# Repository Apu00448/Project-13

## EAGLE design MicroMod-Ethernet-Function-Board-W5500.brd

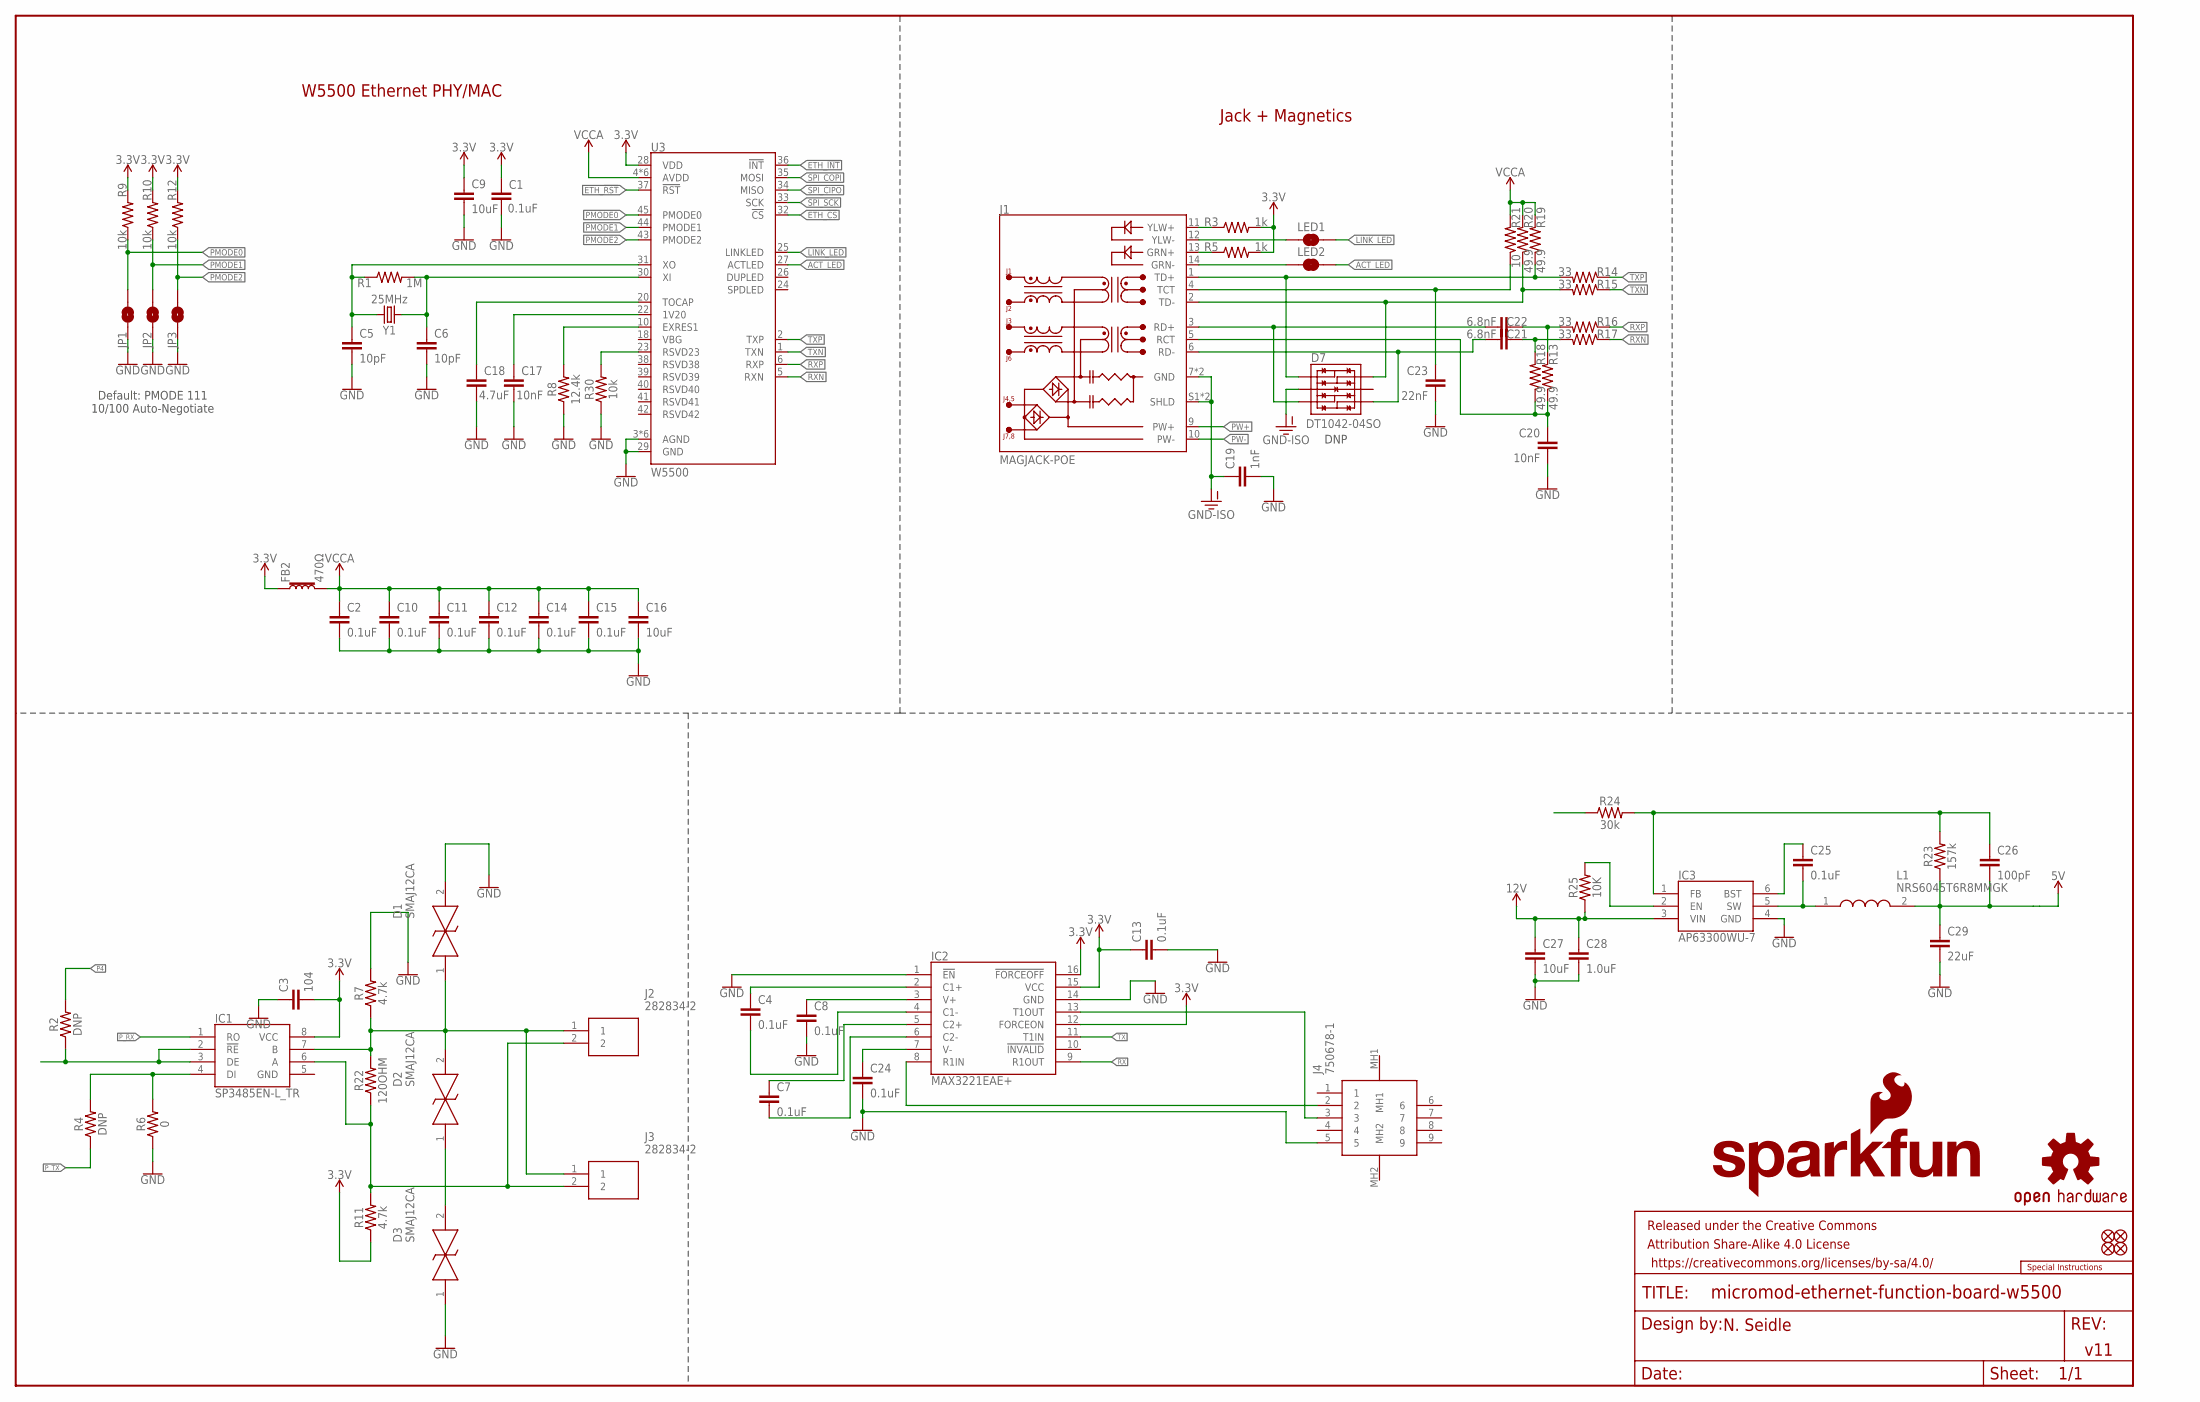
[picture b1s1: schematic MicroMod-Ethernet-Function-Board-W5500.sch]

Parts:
C1, C2, C10, C11, C12, C14, C15: 0.1uF; 0603
C3: 104; 0402-TIGHT_NO_CREAM
C4, C7, C8, C13, C24, C25: 0.1uF; 0402-TIGHT
C5, C6: 10pF; 0603
C9, C16: 10uF; 0603
C17, C20: 10nF; 0603
C18: 4.7uF; 0603
C19: 1nF; 1206
C21, C22: 6.8nF; 0603
C23: 22nF; 0603
C26: 100pF; 0402-TIGHT
C27: 10uF; 0402-TIGHT
C28: 1.0uF; 0402-TIGHT
C29: 22uF; 0603
D1, D2, D3: SMAJ12CA; DIONM5026X229N
D7: DT1042-04SO; SOT-23-6
FB2: 470Ω; 0603
FD1, FD2, FD3, FD4: FIDUCIALUFIDUCIAL; FIDUCIAL-MICRO
FRAME1: FRAME-LEDGER; CREATIVE_COMMONS
IC1: SP3485EN-L_TR; SOIC127P600X175-8N
IC2: MAX3221EAE+; SOP65P778X199-16N
IC3: AP63300WU-7; SOT95P280X90-6N
J1: MAGJACK-POE; MAGJACK-SYM_LED
J2, J3: 282834-2; 282834-2_1
J4: 750678-1; 7506781
JP1, JP2, JP3: JUMPER-SMT_2_NO_SILK; SMT-JUMPER_2_NO_SILK
L1: NRS6045T6R8MMGK
LED1, LED2: JUMPER-SMT_2_NC_TRACE_SILK; SMT-JUMPER_2_NC_TRACE_SILK
LOGO1: SFE_LOGO_NAME_FLAME.1_INCH; SFE_LOGO_NAME_FLAME_.1
LOGO2: SPECIAL_INSTRUCTIONS-ORDERING; ORDERING_INSTRUCTIONS
LOGO3: OSHW-LOGOMINI; OSHW-LOGO-MINI
R1: 1M; 0603
R2, R4: DNP; 0402-TIGHT
R3, R5: 1k; 0603
R6: 0; 0402-TIGHT
R7, R11: 4.7k; 0402-TIGHT
R8: 12.4k; 0603
R9, R10, R12, R30: 10k; 0603
R13, R18, R19, R20: 49.9; 0603
R14, R15, R16, R17: 33; 0603
R21: 10; 0603
R22: 120OHM; 0603
R23: 157k; 0402-TIGHT
R24: 30k; 0402-TIGHT
R25: 10K; 0402-TIGHT
U3: W5500; LQFP-48
Y1: 25MHz; CRYSTAL-SMD-2.0X1.6MM

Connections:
3.3V: C1.1, C3.2, C9.1, C13.1, FB2.1, IC1.8 (VCC), IC2.12 (FORCEON), IC2.15 (VCC), IC2.16 (!FORCEOFF), R3.2, R5.2, R9.2, R10.2, R11.1, R12.2, U3.28 (VDD)
5V: C26.2, C29.1, L1.2, R23.1
12V: C27.1, C28.1, IC3.3 (VIN), R25.1
ACT_LED: LED2.2, U3.27 (ACTLED)
ETH_!CS!: U3.32 (!CS!)
ETH_!INT!: U3.36 (!INT!)
ETH_!RST!: U3.37 (!RST!)
GND: C1.2, C2.2, C3.1, C5.2, C6.2, C8.2, C9.2, C10.2, C11.2, C12.2, C13.2, C14.2, C15.2, C16.2, C17.2, C18.2, C19.2, C20.2, C23.2, C24.2, C27.2, C28.2, C29.2, D1.2, D3.1, IC2.1 (!EN), IC2.14 (GND), IC3.4 (GND), J4.5, JP1.1, JP2.1, JP3.1, R6.1, R7.2, R8.1, R30.1, U3.3 (AGND), U3.9 (AGND), U3.14 (AGND), U3.16 (AGND), U3.19 (AGND), U3.29 (GND), U3.48 (AGND)
GND-ISO: C19.1, D7.2 (VSS), J1.7 (GND), J1.8 (GND), J1.S1 (SHLD), J1.S2 (SHLD)
LINK_LED: LED1.2, U3.25 (LINKLED)
unnamed: C5.1, R1.1, U3.31 (XO), Y1.1
unnamed: C6.1, R1.2, U3.30 (XI), Y1.3 (2)
unnamed: J1.14 (GRN-), LED2.1
unnamed: J1.12 (YLW-), LED1.1
unnamed: C7.1, IC2.5 (C2+)
unnamed: IC1.2 (!RE), IC1.3 (DE), R2.1
unnamed: IC1.4 (DI), R4.2, R6.2
unnamed: J1.13 (GRN+), R5.1
unnamed: C7.2, IC2.6 (C2-)
unnamed: J1.11 (YLW+), R3.1
unnamed: IC1.6 (A), J2.2, J3.2, R11.2, R22.1
unnamed: C4.2, IC2.4 (C1-)
unnamed: R8.2, U3.10 (EXRES1)
unnamed: C4.1, IC2.2 (C1+)
unnamed: C17.1, U3.22 (1V20)
unnamed: C18.1, U3.20 (TOCAP)
unnamed: R30.2, U3.23 (RSVD23)
unnamed: C8.1, IC2.3 (V+)
unnamed: D1.1, D2.2, IC1.7 (B), J2.1, J3.1, R7.1, R22.2
unnamed: D2.1, D3.2
unnamed: C24.1, IC2.7 (V-)
unnamed: C25.2, IC3.5 (SW), L1.1
unnamed: IC2.8 (R1IN), J4.2
unnamed: IC2.13 (T1OUT), J4.3
unnamed: C25.1, IC3.6 (BST)
unnamed: C26.1, IC3.1 (FB), R23.2, R24.2
unnamed: IC3.2 (EN), R25.2
P4: R2.2
PMODE0: JP1.2, R9.1, U3.45 (PMODE0)
PMODE1: JP2.2, R10.1, U3.44 (PMODE1)
PMODE2: JP3.2, R12.1, U3.43 (PMODE2)
PW+: J1.9 (PW+)
PW-: J1.10 (PW-)
P_RX: IC1.1 (RO)
P_TX: R4.1
RCT: C20.1, J1.5 (RCT), R13.1, R18.1
RD+: C22.2, D7.3 (IO2), J1.3 (RD+)
RD-: C21.2, D7.4 (IO3), J1.6 (RD-)
RX: IC2.9 (R1OUT)
RXN: R17.1, U3.5 (RXN)
RXN1: C21.1, R17.2, R18.2
RXP: R16.1, U3.6 (RXP)
RXP1: C22.1, R13.2, R16.2
SPI_CIPO: U3.34 (MISO)
SPI_COPI: U3.35 (MOSI)
SPI_SCK: U3.33 (SCK)
TCT: C23.1, J1.4 (TCT), R21.1
TD+: D7.1 (IO1), J1.1 (TD+), R14.2, R19.1
TD-: D7.6 (IO4), J1.2 (TD-), R15.2, R20.1
TX: IC2.11 (T1IN)
TXN: R15.1, U3.1 (TXN)
TXP: R14.1, U3.2 (TXP)
VCCA: C2.1, C10.1, C11.1, C12.1, C14.1, C15.1, C16.1, FB2.2, R19.2, R20.2, R21.2, U3.4 (AVDD), U3.8 (AVDD), U3.11 (AVDD), U3.15 (AVDD), U3.17 (AVDD), U3.21 (AVDD)

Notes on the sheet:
N. Seidle
v11
W5500 Ethernet PHY/MAC
Default: PMODE 111 10/100 Auto-Negotiate
Jack + Magnetics
DNP

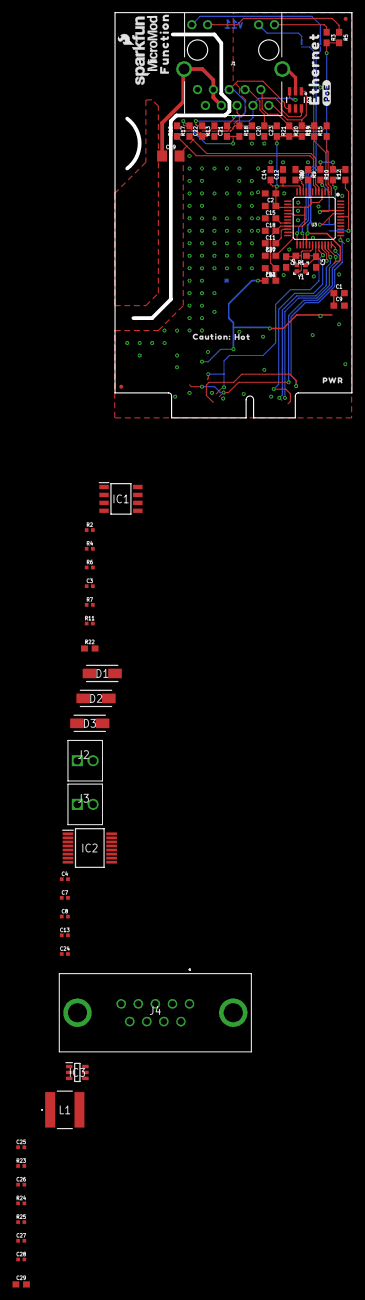
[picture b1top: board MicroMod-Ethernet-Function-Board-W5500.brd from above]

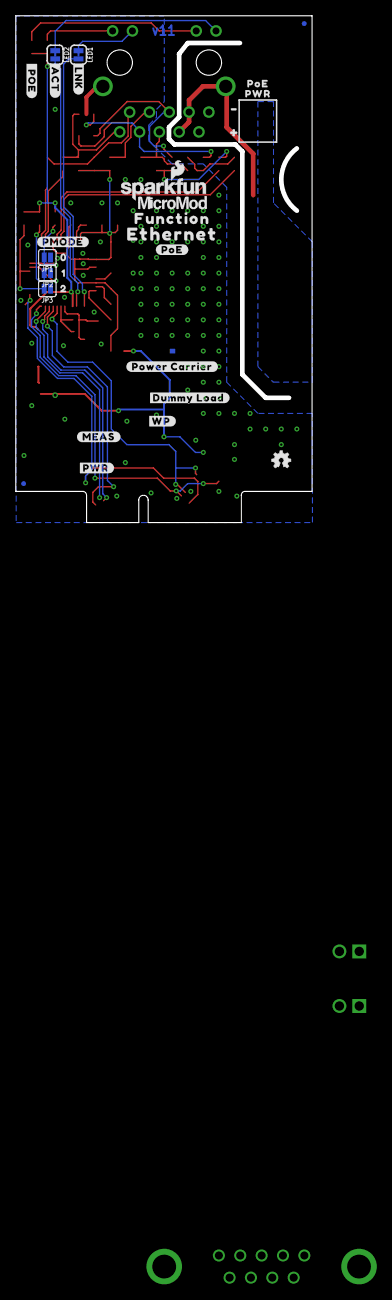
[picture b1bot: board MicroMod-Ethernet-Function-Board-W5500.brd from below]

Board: 2 copper layers, 38.0 x 65.0 mm, 111 parts (29 on the bottom side), 50 nets.

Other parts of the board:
LOGO4: SFE_LOGO_NAME_FLAME.1_INCH; SFE_LOGO_NAME_FLAME_.1
U$1, U$17: ETHERNET0
U$2, U$18: #POE#0
U$3: #POWER_CARRIER#0
U$5: #DUMMY_LOAD#0
U$6: #WP#0
U$7: PWR0
U$8: #ACT#0
U$9: POE0
U$12: #LNK#1
U$13: #PMODE#0
U$14: 01
U$15: 12
U$16: 23
U$19: #0
U$20: CAUTION#0
U$21: HOT#1
U$22: #PWR#0
U$23: #_POE#0
U$24: PWR1
U$25: #1
U$26, U$27: FUNCTION0
U$28: #MEAS#3
U$37, U$63: MICROMOD_LOGO_.35

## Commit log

2024-01-03 MicroMod-Ethernet-Board_ Eagle

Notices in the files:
parts and their libraries:
SparkFun-Aesthetics: Licensing: Creative Commons ShareAlike 4.0 International - https://creativecommons.org/licenses/by-sa/4.0
SparkFun-Aesthetics: Released under the Creative Commons Attribution Share-Alike 4.0 License
SparkFun-Aesthetics: https://creativecommons.org/licenses/by-sa/4.0
